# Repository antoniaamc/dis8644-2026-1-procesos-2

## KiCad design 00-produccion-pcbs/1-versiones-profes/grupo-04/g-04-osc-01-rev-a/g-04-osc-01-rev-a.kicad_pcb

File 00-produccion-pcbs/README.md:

# produccion-pcbs

jornada maratónica sábado 06 junio 2026

equipo docente toma todos los proyectos de kicad entregados el día anterior, de proyecto-02, y con eso edita, revisa, y envía a producción.

hay 6 grupos de trabajo con una temática en particular, cada grupo realizó 2 esquemáticos con sus respectivas placas, en varias versiones que subieron a la carpeta 00-proyecto-02.

a continuación los apuntes de las distintas revisiones hechas de estos proyectos, para prepararlos para su producción física.

en este repo creamos 4 carpetas:

- 0-versiones-estudiantes: archivos de kicad con las versiones más recientes de proyectos de estudiantes
- 1-versiones-profes: archivos de kicad con las versiones revisadas y realizadas por equipo docentes
- 2-archivos-produccion: gerbers de producción, etiquetados como rev-a.
- 3 archivos-produccion-zip: cada carpeta comprimida en .zip, para el envío a la fábrica jlcpcb.

## grupo-01: piezos

- benjaminalvarez21
- Anaysval
- chknngttts
- ryukivol
- nicolasvaldesgreve

### g-01-pie-01-rev-a

- cambiamos tamaño r15
- cambiamos conector de entrada
- cambiamos nomenclatura de "100 u" a "100u"
- cambiamos huella de transistor Q1, porque era la equivocada

### g-01-pie-02-rev-a

- no fue enviado a producción porque no tenemos garantía de que funcionara según lo visto en protoboard.

## grupo-02: secuenciadores

- isidoraalvarez
- tomascatri
- dayanapanitrur
- Estrabismx
- angel-udp

### g-02-sec-01-rev-a

en esquemático:

- agregamos resistor de clock in a ground, para pulldown.
- agregamos resistor entre 4040 Q0 patita 9 y salida
- agregamos resistor a cada salida de jack switch.
- cambiamos huellas de transistores a versión inline_wide para que tengan más espacio
- agregados mounting hole faltantes

en pcb:

- actualizamos conectores jack a la huella de la biblioteca, para poder rutear bien los nuevos resistores y no perdernos.

### g-02-sec-02-rev-a

en esquemático:

- agregamos también resistores de protección en entradas y salidas.
- agregados mounting hole faltantes

en pcb:

- actualizamos conectores jack a la huella de la biblioteca, para poder rutear bien los nuevos resistores y no perdernos.

## grupo-03: osciladores 1

- vanessagarciaM
- antoloch
- ccarlabelenn
- arielorozco024
- Narelyriquelme

### g-03-osc-01-rev-a

- C1 estaba rotado, fue corregido.
- audio jack de entrada y salida estaban mal conectados
- condensador de salida fue cambiado por uno no polarizado

### g-03-osc-02-rev-a

- renombrar C3 a 4u7
- cambiado C1 por condensador polarizado
- 40106 fue usado como dos chips distintos, en vez de usar varios schmitt triggers desde un mismo chip, tuvimos que hacer esos cambios
- volvimos a rutear casi todo, ya que se bajó de 2 chips a 1

## grupo-04: osciladores 2

- antokiaraa
- santiagocifuvelez
- paulafuentesm
- kristelagj
- catalinaoyanedel
- yairaruiz

### g-04-osc-01-rev-a

- borramos amplificador para que esté en otro módulo
- agregamos resistencia de salida
- conectamos bien el jack de salida de audio que tenía problemas

### g-04-osc-02-rev-a

- borramos amplificador para que esté en otro módulo
- agregamos valor a diodo faltante
- corregimos símbolo de los potenciómetros
- agregamos resistencia de salida
- agregamos jack de salida de audio

## grupo-05: filtros

- antoniaamc
- Catabalboa
- sebastianguevaralarotta
- CatalinaJeria
- Luisaatoro9

### g-05-fil-01-rev-a

- error grave en la nomenclatura de los proyectos: el 01 en su README dicen que es el activo, pero en Kicad es el pasivo
- cambiamos C1 por condensador no polarizado
- conectamos patita del medio de potenciómetro
- confusión en los tamaños de los condensadores C4 y C5
- los tamaños de las pistas usados no fueron los indicados en clases ni en estandarización
- faltó el paso de agregar tierra a la placa, no está hecho

### g-05-fil-02-rev-a

- error grave en la nomenclatura de los proyectos: el 01 en su README dicen que es el activo, pero en Kicad es el pasivo
- no fue enviado a producción, ya que no funcionó en protoboard

## grupo-06: percusiones

- terroiblea
- martinaechavarria-stack
- Nicolas-Miranda1312
- paredesvania
- Coff4

### g-06-perc-01-rev-a

- agregamos jack de entrada de audio que reemplace la oscilación de entrada
- agregamos ground a los integrados que no están siendo usados

### g-06-perc-02-rev-a

- agregamos el detalle de las entradas de las compuertas lógicas no usadas, fueron conectadas a tierra, para definir sus estados
- C7 estaba en el esquemático pero no en la placa, tuvimos que agregarlo
- C4 le faltaba una conexión en la PCB, la agregamos

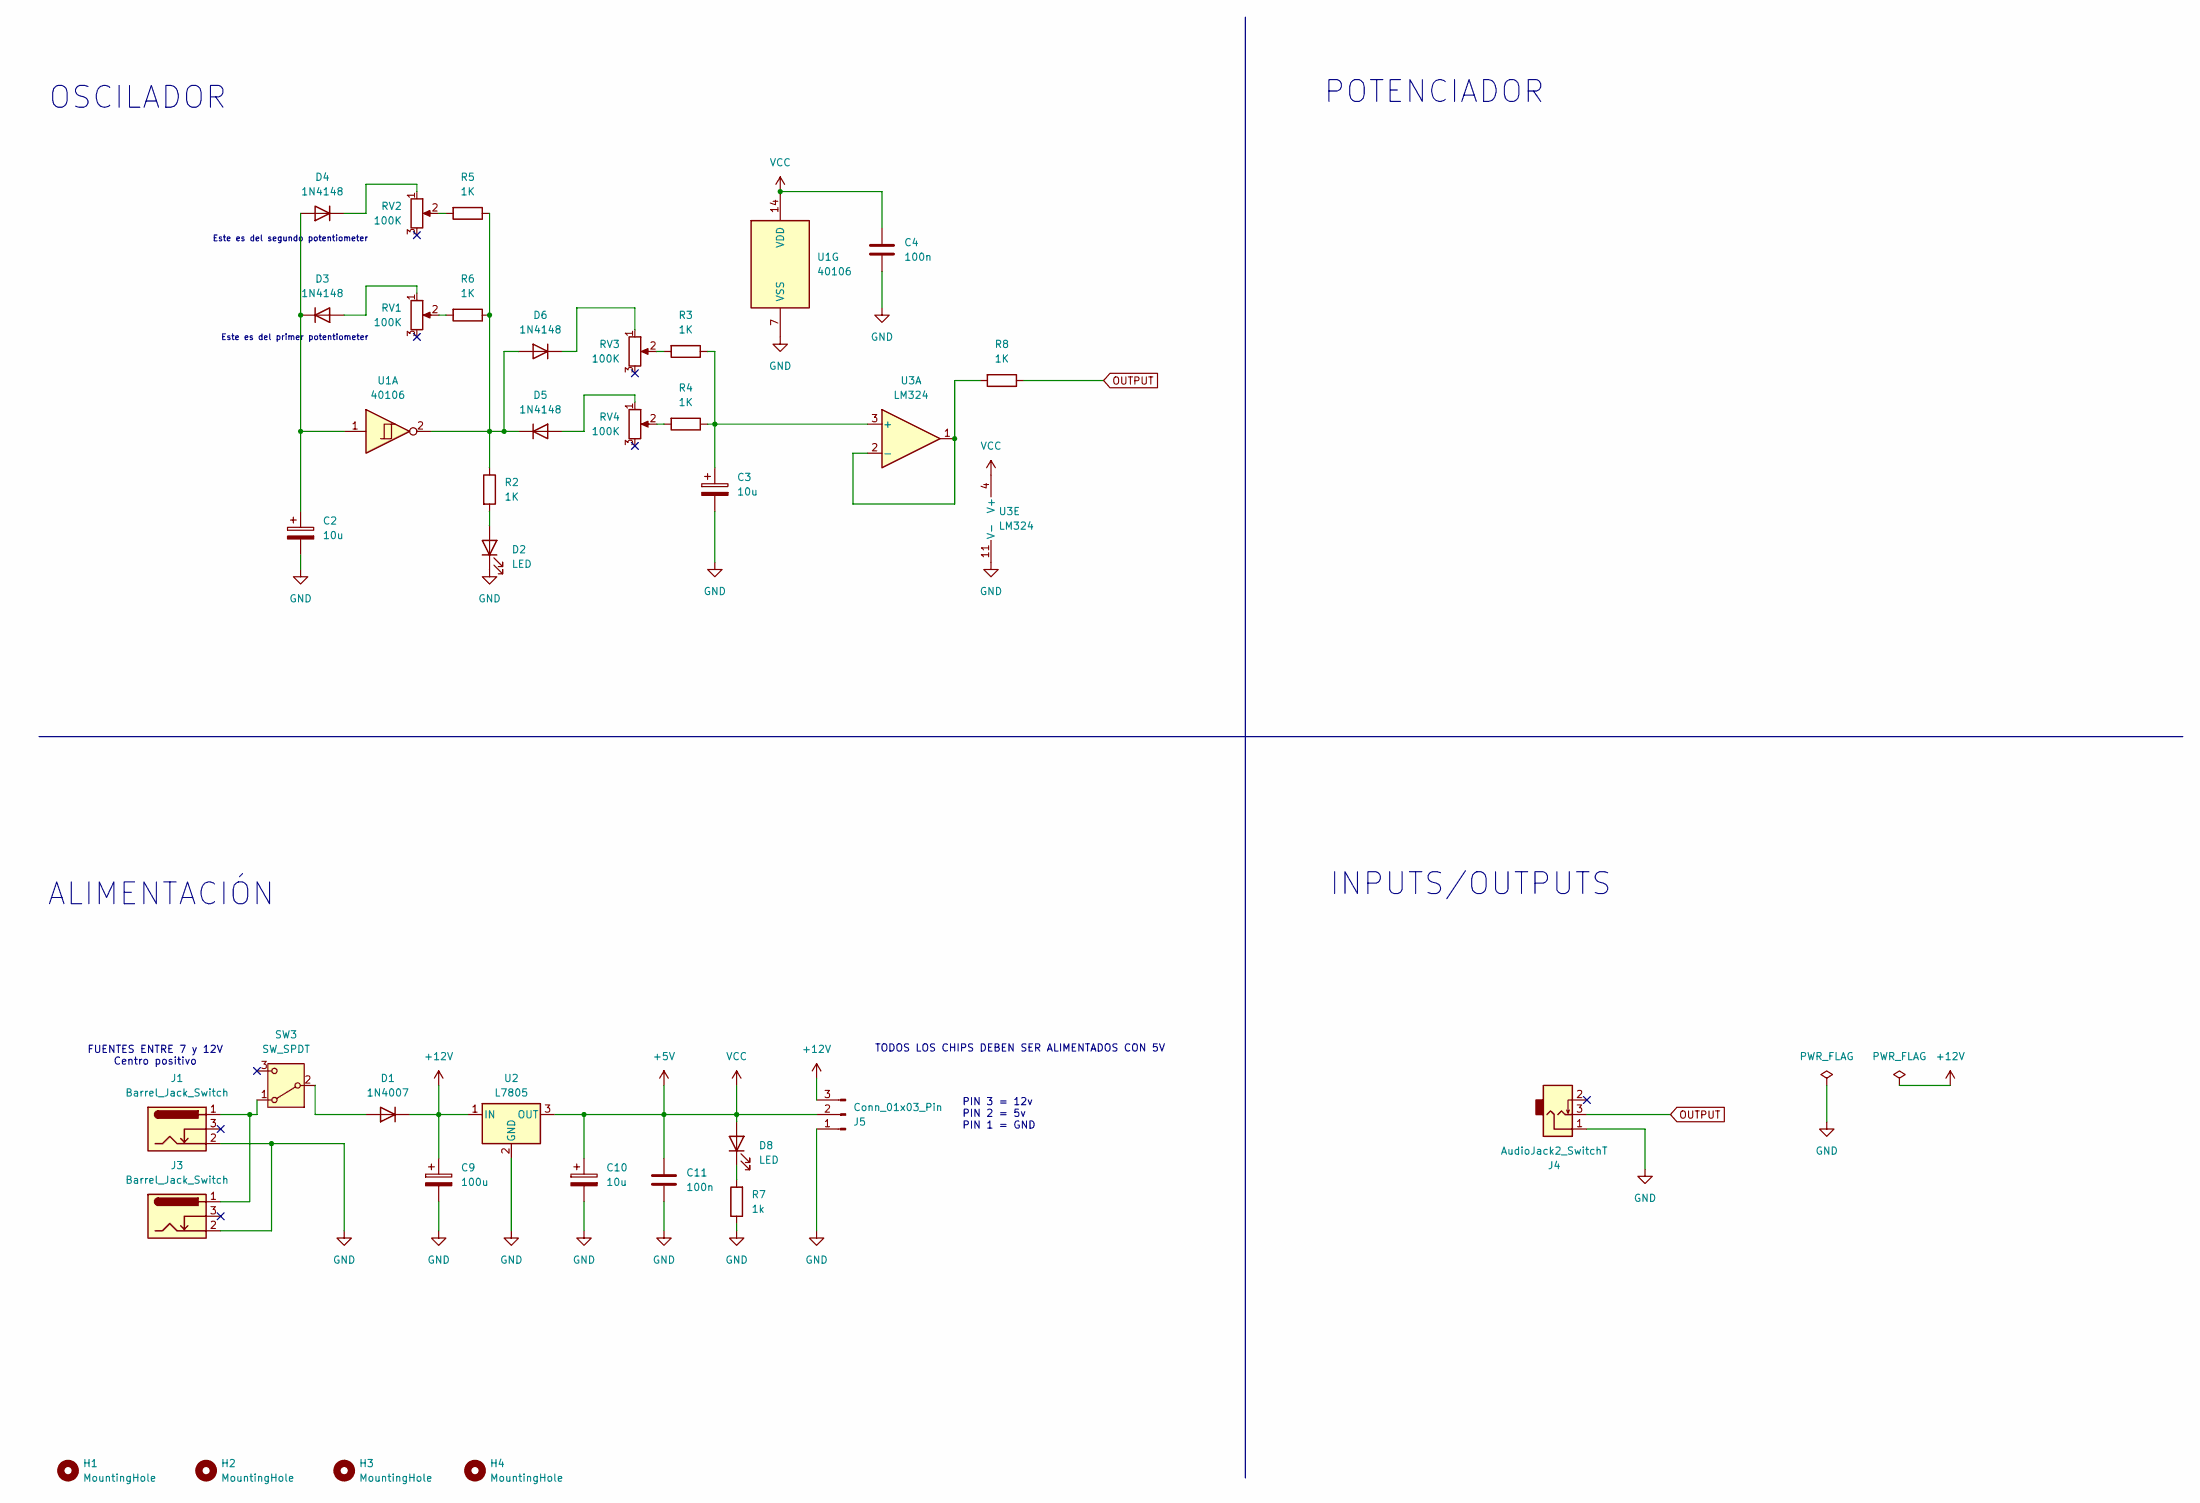
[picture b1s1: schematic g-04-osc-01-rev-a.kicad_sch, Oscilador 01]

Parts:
C2, C3, C10: 10u; CP_Radial_D4.0mm_P2.00mm
C4, C11: 100n; C_Disc_D5.0mm_W2.5mm_P2.50mm
C9: 100u; CP_Radial_D8.0mm_P3.80mm
D1: 1N4007; D_DO-41_SOD81_P10.16mm_Horizontal
D2, D8: LED; LED_D5.0mm
D3, D4, D5, D6: 1N4148; D_DO-35_SOD27_P7.62mm_Horizontal
H1, H2, H3, H4: MountingHole; MountingHole_3.2mm_M3
J1, J3: Barrel_Jack_Switch; BarrelJack_Horizontal
J4: AudioJack2_SwitchT; PJ301M-12
J5: Conn_01x03_Pin; PinSocket_1x03_P2.54mm_Vertical
R2, R3, R4, R5, R6, R8: 1K; R_Axial_DIN0207_L6.3mm_D2.5mm_P10.16mm_Horizontal
R7: 1k; R_Axial_DIN0207_L6.3mm_D2.5mm_P10.16mm_Horizontal
RV1, RV2, RV3, RV4: 100K; Potentiometer_Alps_RK163_Single_Horizontal
SW3: SW_SPDT; spdt_ssd12d00g3
U1: 40106; DIP-14_W7.62mm
U2: L7805; TO-220-3_Horizontal_TabDown
U3: LM324; DIP-14_W7.62mm

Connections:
+5V: C4.1, C10.1, C11.1, D8.2 (A), J5.2, U1.14 (VDD), U2.3 (OUT), U3.4 (V+)
+12V: C9.1, D1.1 (K), J5.3, U2.1 (IN)
GND: C2.2, C3.2, C4.2, C9.2, C10.2, C11.2, D2.1 (K), J1.2, J3.2, J4.1, J5.1, R7.1, U1.7 (VSS), U2.2 (GND), U3.11 (V-)
unnamed: D1.2 (A), SW3.2 (B)
unnamed: D2.2 (A), R2.2
unnamed: D3.2 (A), RV1.1
unnamed: C2.1, D3.1 (K), D4.2 (A), U1.1
unnamed: D4.1 (K), RV2.1
unnamed: D5.2 (A), RV4.1
unnamed: D5.1 (K), D6.2 (A), R2.1, R5.1, R6.1, U1.2
unnamed: D6.1 (K), RV3.1
unnamed: D8.1 (K), R7.2
unnamed: R3.2, RV3.2
unnamed: R4.2, RV4.2
unnamed: R5.2, RV2.2
unnamed: R6.2, RV1.2
unnamed: J1.1, J3.1, SW3.1 (A)
unnamed: C3.1, R3.1, R4.1, U3.3 (+)
unnamed: R8.2, U3.1, U3.2 (-)
OUTPUT: J4.3, R8.1

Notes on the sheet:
ALIMENTACIÓN
Este es del segundo potentiometer
INPUTS/OUTPUTS
PIN 3 = 12v PIN 2 = 5v PIN 1 = GND
POTENCIADOR
Este es del primer potentiometer
OSCILADOR
TODOS LOS CHIPS DEBEN SER ALIMENTADOS CON 5V
FUENTES ENTRE 7 y 12V Centro positivo

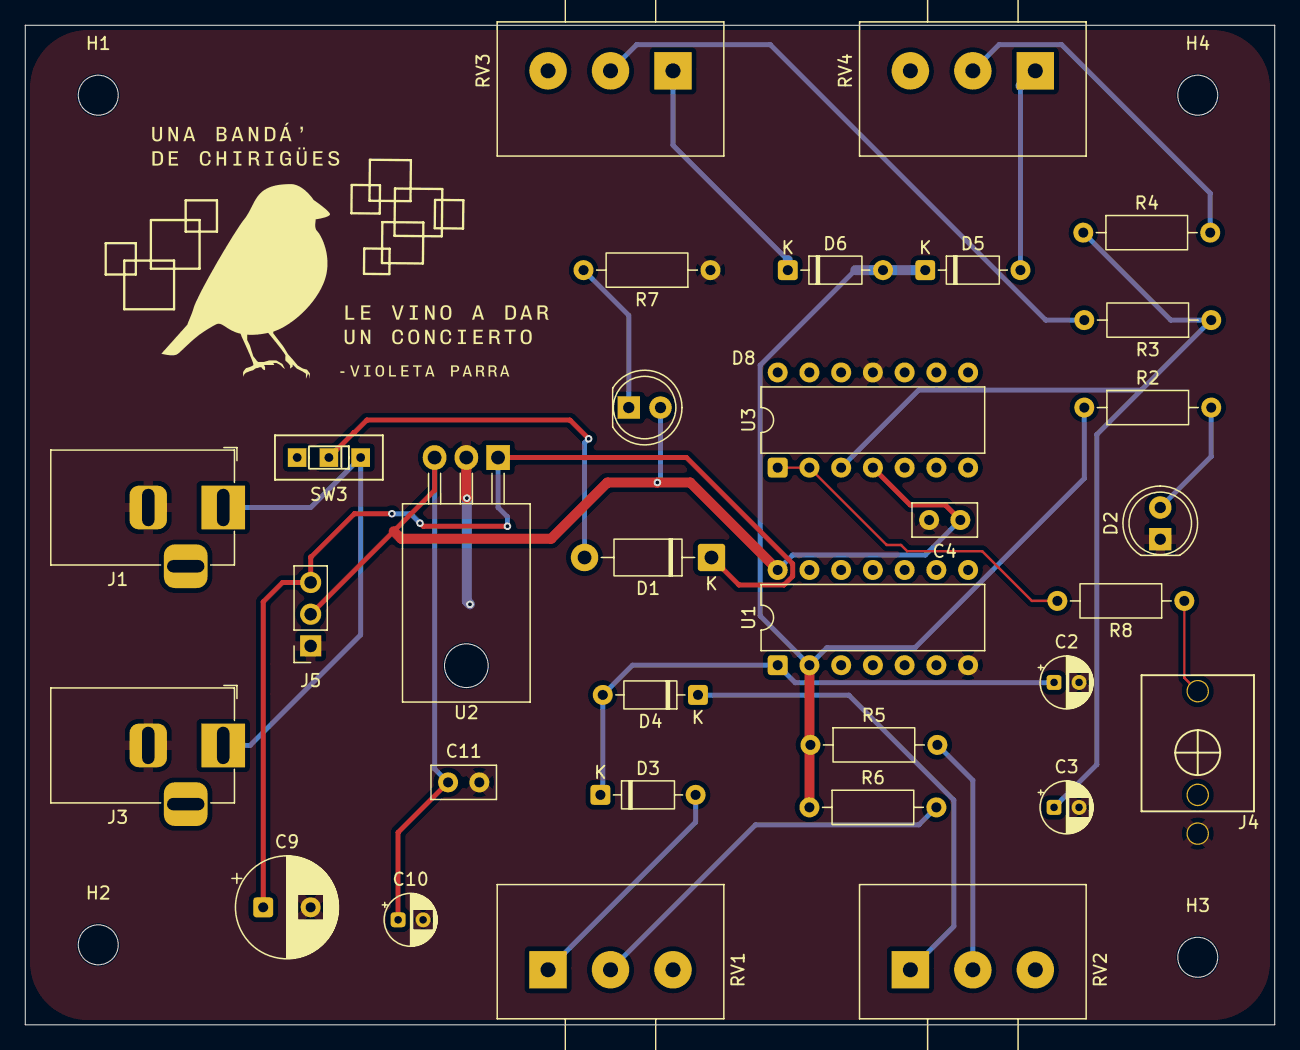
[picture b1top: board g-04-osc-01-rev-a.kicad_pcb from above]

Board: 2 copper layers, 100.0 x 80.0 mm, 36 parts (0 on the bottom side), 20 nets.

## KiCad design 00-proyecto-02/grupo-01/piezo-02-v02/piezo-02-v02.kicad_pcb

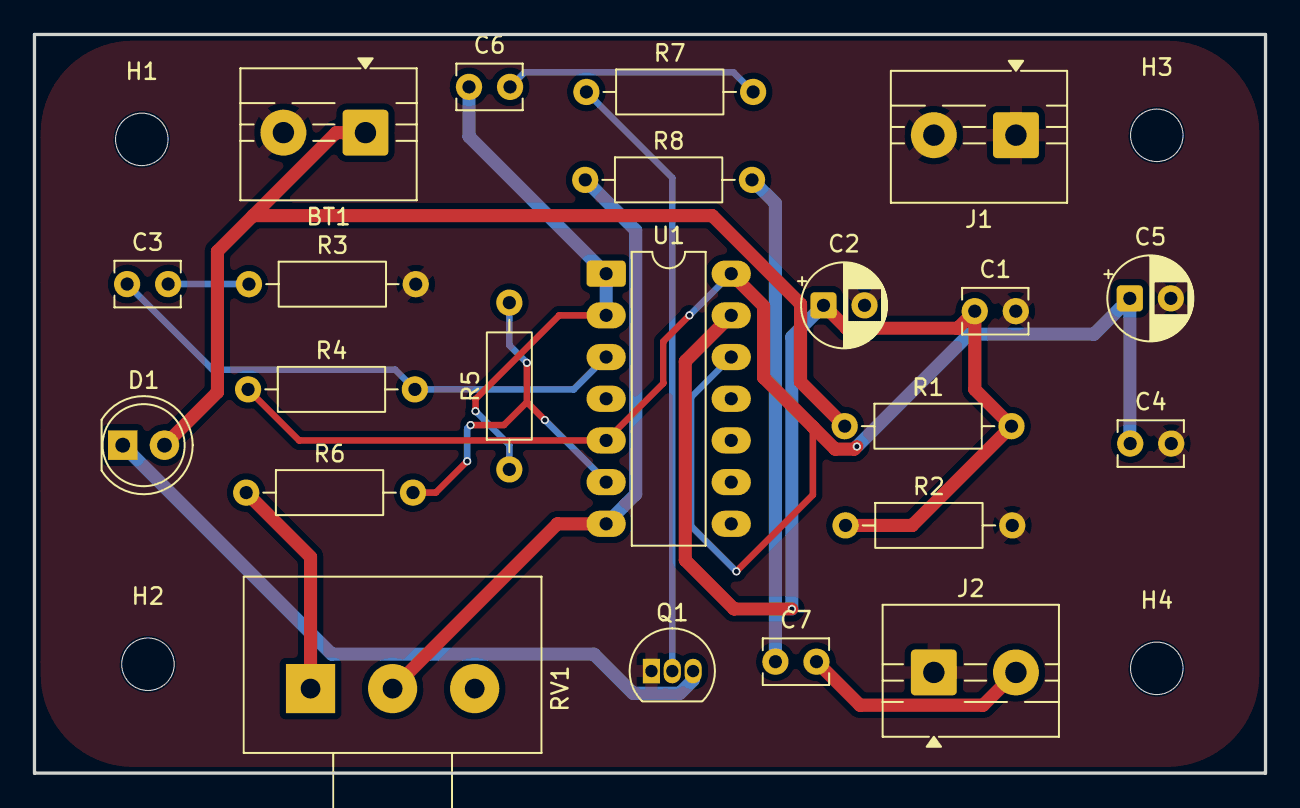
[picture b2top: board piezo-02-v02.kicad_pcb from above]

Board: 2 copper layers, 75.0 x 45.0 mm, 26 parts (0 on the bottom side), 15 nets.

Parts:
BT1: Battery_Cell; TerminalBlock_MaiXu_MX126-5.0-02P_1x02_P5.00mm
C1, C4, C6, C7: 10u; C_Disc_D3.8mm_W2.6mm_P2.50mm
C2, C5: 100n; CP_Radial_D5.0mm_P2.50mm
C3: 1u; C_Disc_D3.8mm_W2.6mm_P2.50mm
D1: LED; LED_D5.0mm
H1, H2, H3, H4: M3; MountingHole_3.2mm_M3
J1, J2: TTS; TerminalBlock_MaiXu_MX126-5.0-02P_1x02_P5.00mm
Q1: PN2222A; TO-92_Inline
R1, R2, R4: 100k; R_Axial_DIN0207_L6.3mm_D2.5mm_P10.16mm_Horizontal
R3: 3M; R_Axial_DIN0207_L6.3mm_D2.5mm_P10.16mm_Horizontal
R5: 10k; R_Axial_DIN0207_L6.3mm_D2.5mm_P10.16mm_Horizontal
R6, R8: 1k; R_Axial_DIN0207_L6.3mm_D2.5mm_P10.16mm_Horizontal
R7: 22k; R_Axial_DIN0207_L6.3mm_D2.5mm_P10.16mm_Horizontal
RV1: 500k; Potentiometer_Alps_RK163_Single_Horizontal
U1: LM324; DIP-14_W7.62mm_LongPads

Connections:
GND: BT1.2 (-), C1.2, C2.2, C4.2, C5.2, J1.1, J1.2, J2.1, Q1.1 (E), R2.2, R3.2
unnamed: C3.2, R3.1
unnamed: C6.2, R7.2
unnamed: C7.1, R8.2
unnamed: C7.2, J2.2
unnamed: D1.1 (K), Q1.3 (C)
unnamed: Q1.2 (B), R7.1
unnamed: R6.1, RV1.1
unnamed: R8.1, RV1.2, U1.7
unnamed: C3.1, R4.2, U1.3 (+)
unnamed: C6.1, R5.1, U1.1, U1.2 (-)
unnamed: R5.2, R6.2, U1.6 (-)
unnamed: C1.1, C2.1, R1.2, R2.1, U1.13 (-)
VBUS: C4.1, C5.1, R4.1, U1.5 (+), U1.12 (+), U1.14
VCC: BT1.1 (+), D1.2 (A), R1.1

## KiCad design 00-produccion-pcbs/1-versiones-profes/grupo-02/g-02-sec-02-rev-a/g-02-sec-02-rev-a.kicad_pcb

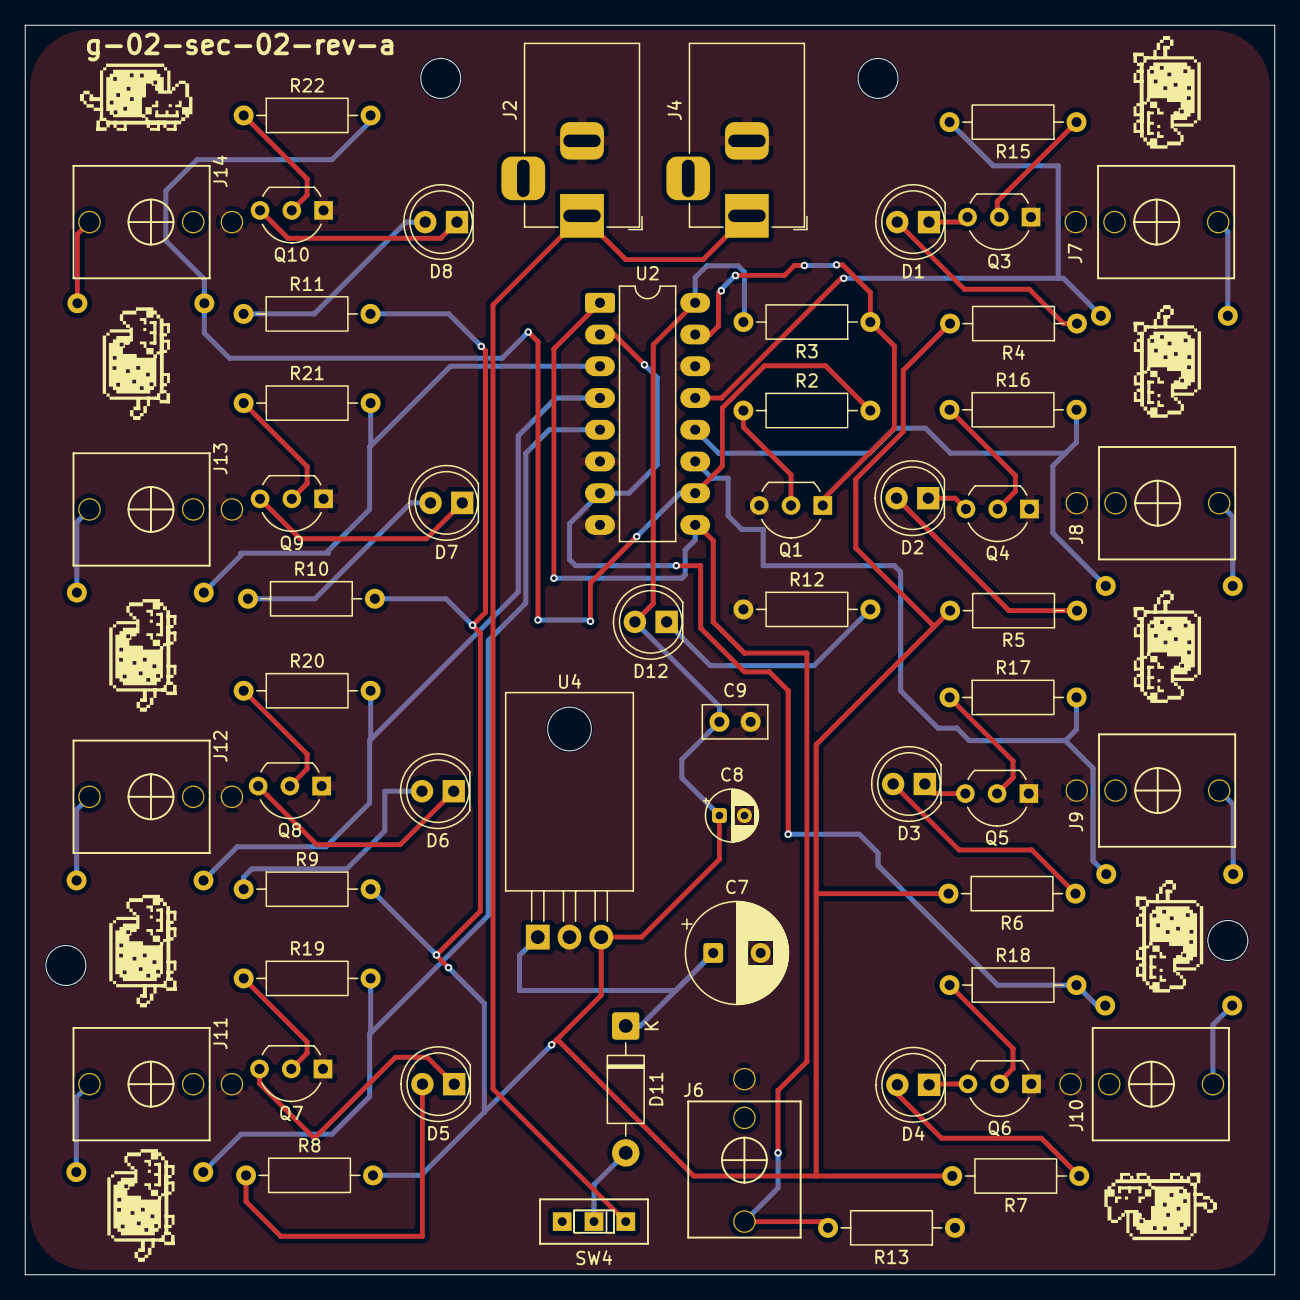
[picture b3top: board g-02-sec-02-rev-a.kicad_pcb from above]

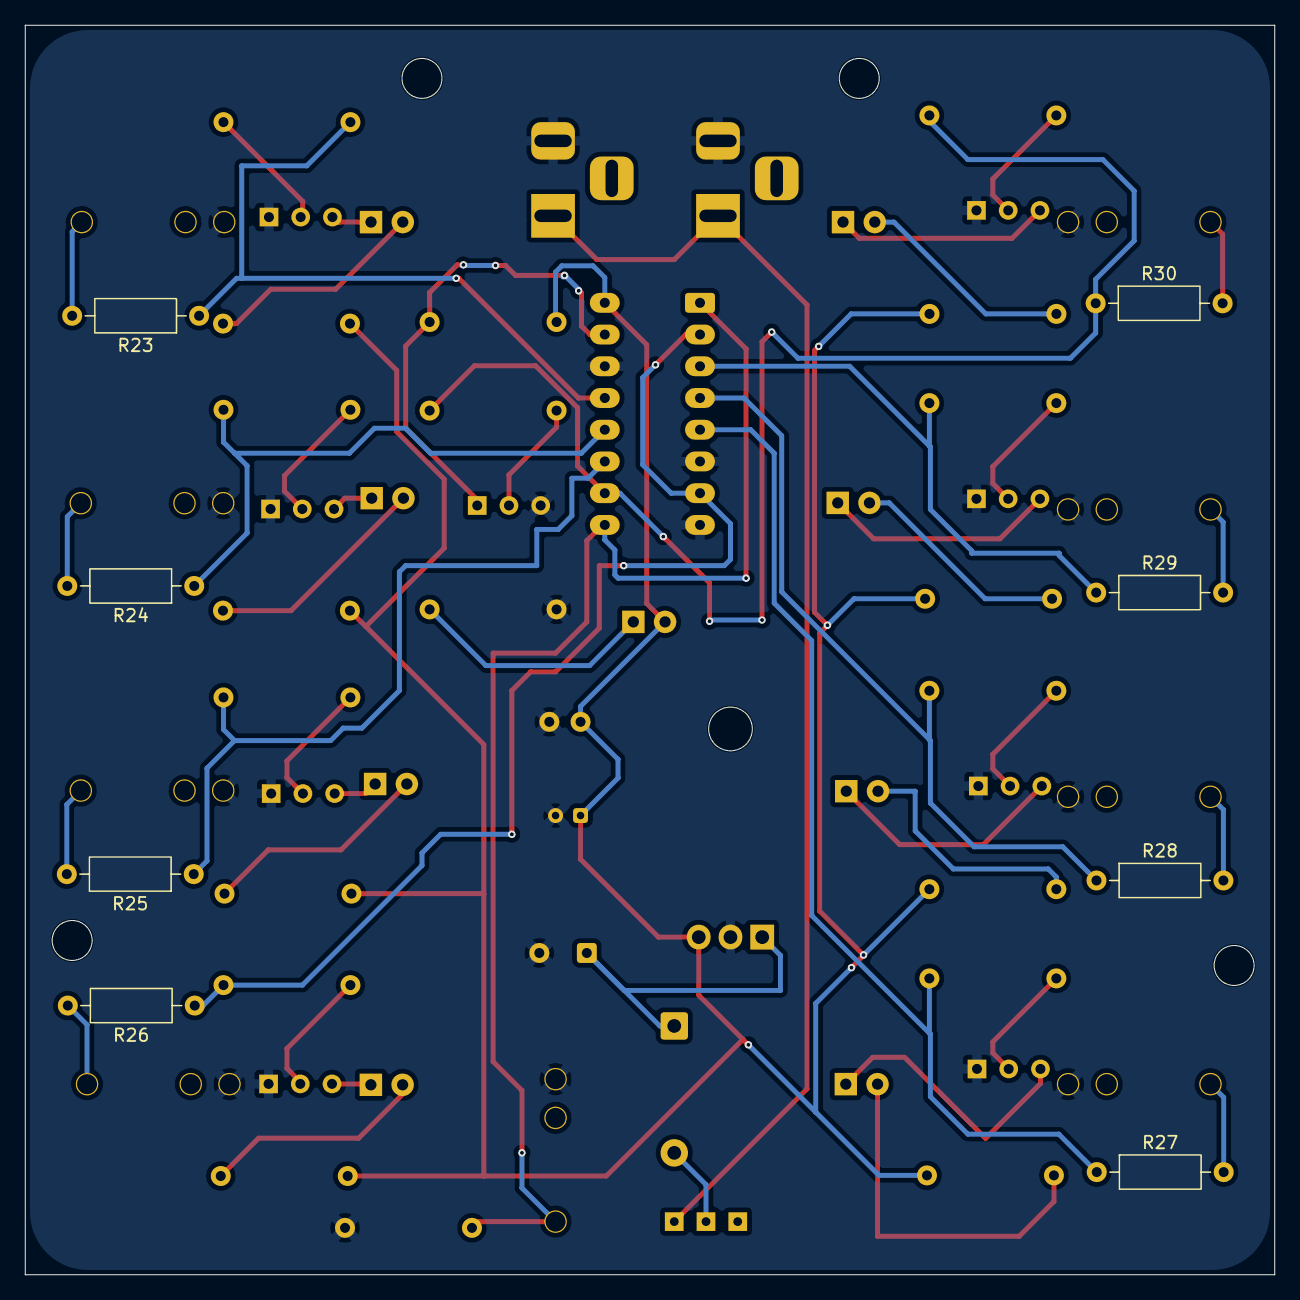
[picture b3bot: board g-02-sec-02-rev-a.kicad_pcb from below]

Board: 2 copper layers, 100.0 x 100.0 mm, 68 parts (8 on the bottom side), 49 nets.

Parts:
C7: 100u; CP_Radial_D8.0mm_P3.80mm
C8: 10u; CP_Radial_D4.0mm_P2.00mm
C9: 100n; C_Disc_D5.0mm_W2.5mm_P2.50mm
D1, D2, D3, D4, D5, D6, D7, D8, D12: LED; LED_D5.0mm
D11: 1N4007; D_DO-41_SOD81_P10.16mm_Horizontal
H1, H2, H3, H4: M3; MountingHole_3.2mm_M3
J2, J4: Barrel_Jack_Switch; BarrelJack_Horizontal
J6, J7, J8, J9, J10, J11, J12, J13, J14: AudioJack2_SwitchT; PJ301M-12
Q1: BC548; TO-92_Inline_Wide
Q3, Q4, Q5, Q6, Q7, Q8, Q9, Q10: PN2222A; TO-92_Inline_Wide
R2: 10k; R_Axial_DIN0207_L6.3mm_D2.5mm_P10.16mm_Horizontal
R3, R12, R15, R16, R17, R18, R19, R20, R21, R22, R23, R24, R25, R26, R27, R28, R29, R30: 1k; R_Axial_DIN0207_L6.3mm_D2.5mm_P10.16mm_Horizontal
R4, R5, R6, R7, R8, R9, R10, R11: 220; R_Axial_DIN0207_L6.3mm_D2.5mm_P10.16mm_Horizontal
R13: 100k; R_Axial_DIN0207_L6.3mm_D2.5mm_P10.16mm_Horizontal
SW4: SW_SPDT; spdt_ssd12d00g3
U2: 4015; DIP-16_W7.62mm_LongPads
U4: L7805; TO-220-3_Horizontal_TabDown

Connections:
+5V: C8.1, C9.1, D12.2 (A), R3.2, R4.2, R5.2, R6.2, R7.2, R8.2, R9.2, R10.2, R11.2, U2.16 (Vdd), U4.3 (OUT)
+12V: C7.1, D11.1 (K), U4.1 (IN)
GND: C7.2, C8.2, C9.2, J2.2, J4.2, J6.1, J7.1, J8.1, J9.1, J10.1, J11.1, J12.1, J13.1, J14.1, Q1.3 (E), Q3.1 (E), Q4.1 (E), Q5.1 (E), Q6.1 (E), Q7.1 (E), Q8.1 (E), Q9.1 (E), Q10.1 (E), R12.1, R13.1, U2.6 (MR), U2.8 (Vss), U2.14 (MR), U4.2 (GND)
unnamed: D1.2 (A), R4.1
unnamed: D1.1 (K), Q3.3 (C)
unnamed: D2.2 (A), R5.1
unnamed: D2.1 (K), Q4.3 (C)
unnamed: D3.2 (A), R6.1
unnamed: D3.1 (K), Q5.3 (C)
unnamed: D4.2 (A), R7.1
unnamed: D4.1 (K), Q6.3 (C)
unnamed: D5.2 (A), R8.1
unnamed: D5.1 (K), Q7.3 (C)
unnamed: D6.2 (A), R9.1
unnamed: D6.1 (K), Q8.3 (C)
unnamed: D7.2 (A), R10.1
unnamed: D7.1 (K), Q9.3 (C)
unnamed: D8.2 (A), R11.1
unnamed: D8.1 (K), Q10.3 (C)
unnamed: D11.2 (A), SW4.2 (B)
unnamed: D12.1 (K), R12.2
unnamed: J7.3, R23.2
unnamed: J8.3, R24.2
unnamed: J9.3, R25.2
unnamed: J10.3, R26.2
unnamed: J11.3, R27.2
unnamed: J12.3, R28.2
unnamed: J13.3, R29.2
unnamed: J14.3, R30.2
unnamed: Q1.2 (B), R2.1
unnamed: Q1.1 (C), R3.1, U2.15 (D)
unnamed: Q3.2 (B), R15.1
unnamed: Q4.2 (B), R16.1
unnamed: Q5.2 (B), R17.1
unnamed: Q6.2 (B), R18.1
unnamed: Q7.2 (B), R19.1
unnamed: Q8.2 (B), R20.1
unnamed: Q9.2 (B), R21.1
unnamed: Q10.2 (B), R22.1
unnamed: J2.1, J4.1, SW4.1 (A)
unnamed: J6.3, R13.2, U2.1 (CP), U2.9 (CP)
unnamed: R18.2, R26.1, U2.2 (Q4), U2.7 (D)
unnamed: R19.2, R27.1, U2.5 (Q1)
unnamed: R20.2, R28.1, U2.4 (Q2)
unnamed: R21.2, R29.1, U2.3 (Q3)
unnamed: R2.2, R22.2, R30.1, U2.10 (Q4)
unnamed: R15.2, R23.1, U2.13 (Q1)
unnamed: R16.2, R24.1, U2.12 (Q2)
unnamed: R17.2, R25.1, U2.11 (Q3)

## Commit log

2026-05-15 Rename imagen4.PNG to imagen4.Ppng
2026-05-15 Update README with session notes and observations
    Added notes and observations from the session, including issues encountered and solutions applied.
2026-05-18 Update README with class reflections and KiCad project steps
    Added reflections on online class experience and detailed steps for KiCad project creation, including personal progress and learnings.
2026-05-18 Add new sections on images and text interpretation
2026-05-19 Add holiday break note to README
2026-05-19 Add notes to README for sesion-10a
2026-05-22 arreglo apuntes
2026-05-22 Update README with class notes and reflections
2026-05-22 cambiar a relativo
2026-05-24 cap 1
    Added notes and reflections on Flusser's book, discussing the significance of images and their role in society.
2026-05-25 Revisar bien
2026-05-25 Fix formatting and add sections in README.md
2026-05-26 Expand README with Flusser's insights on photography
    Added discussion on the nature of photography and technical images according to Flusser.
2026-05-26 Enhance README with insights on photography and memory
    Added a detailed comparison of photography and hunting, discussing the conditional freedom of photographers and the transformative nature of photographs in shaping memory.
2026-05-29 Update README with session notes and circuit details
    Added detailed class session notes and circuit testing steps.
2026-05-31 arreglo redacción
2026-05-31 eliminar archivo borrar
2026-06-01 agrego un poco de apuntes
2026-06-02 Revise assignment title and description in README
    Updated the section title and clarified the assignment details.
2026-06-02 Delete content from README.md
    Removed the entire content of the README.md file, including sections on the class and discussions.
2026-06-02 Update README with project details and images
    Added images and additional context for project two.
2026-06-03 agregar heaer
2026-06-04 agrego esquematico
2026-06-05 Enhance README with detailed circuit descriptions
    Updated descriptions and added details about the circuit's functionality and components. Included development phases and improved clarity in explanations.
2026-06-05 Create oscilador-02-v03-0506
2026-06-06 agregar carpeta para produccion pcbs
2026-06-06 agregar apuntes
2026-06-06 agregar README
2026-06-06 estandarizar nombres
2026-06-06 corregido 02-02
2026-06-06 uploaded g-04-01
2026-06-06 agregar info de las carpetas
2026-06-12 en edicion
    Updated image paths and added new images to README.
2026-06-14 Condense analysis of chapters 4 and 5 in README.md
2026-06-16 Add image to README
    Added an image to the README file.
2026-06-17 agrego apuntes
2026-06-18 agrego pequeño
2026-06-18 agrego créditos a bruno
2026-06-19 arreglo bom
2026-06-19 disco-imagen
2026-06-23 Update README.md for sesion-12b
    Added section header for 'sesion-12b' and removed previous content.
2026-06-23 libro-tarde-mala-mia
